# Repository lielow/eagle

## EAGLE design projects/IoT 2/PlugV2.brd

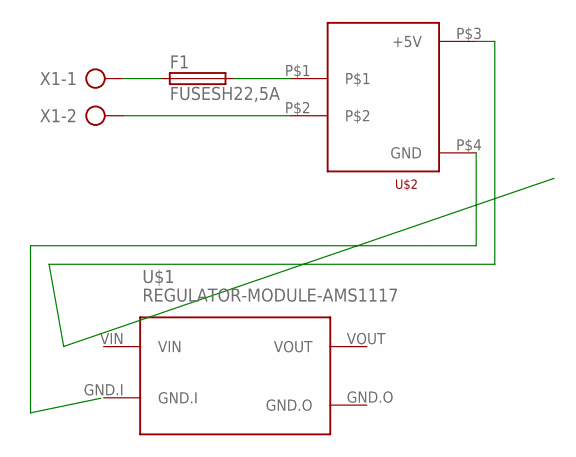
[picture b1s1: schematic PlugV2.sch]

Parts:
F1: FUSESH22,5A; SH22,5A
U$1: REGULATOR-MODULE-AMS1117
U$2: HLK-PM01
X1: AK300/2

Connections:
unnamed: F1.1, X1.1
unnamed: U$2.P$2, X1.2
unnamed: F1.2, U$2.P$1

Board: 2 copper layers, 4 parts (0 on the bottom side), 3 nets, no tracks yet.

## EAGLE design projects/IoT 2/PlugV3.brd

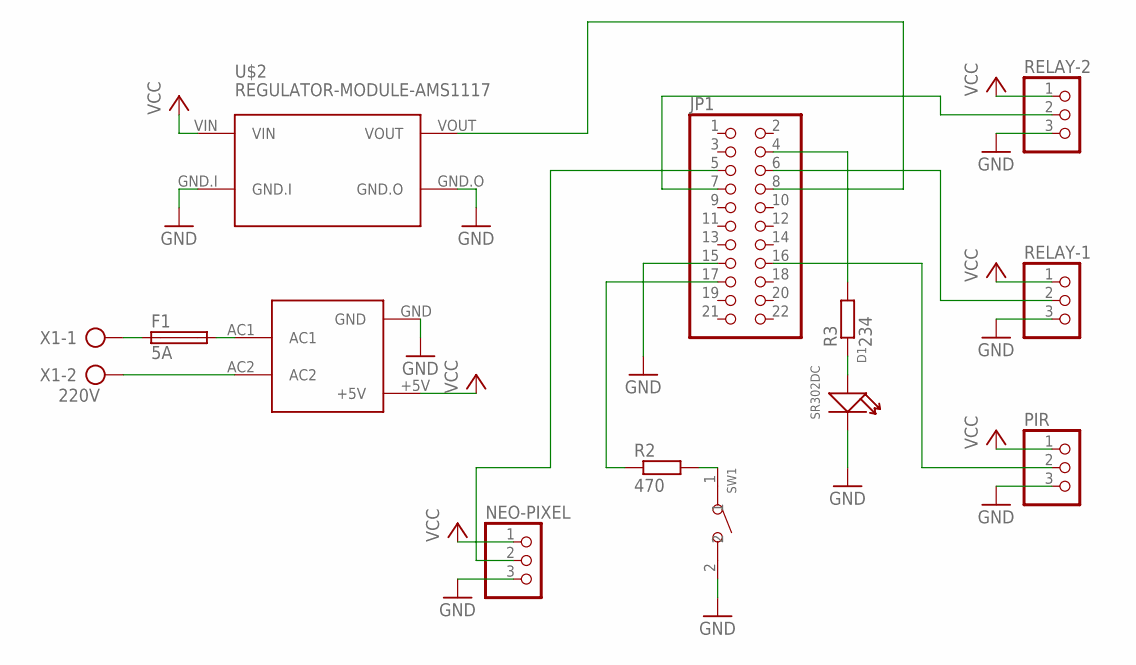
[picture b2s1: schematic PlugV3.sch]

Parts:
D1: SR302DC; LED2-2.54-D3.0MM
F1: 5A; SH22,5A
JP1: PINHD-2X11; 2X11
NEO-PIXEL: PINHD-1X3; 1X03
PIR: PINHD-1X3; 1X03
R2: 470; 0207/7
R3: 234; 0207/7
RELAY-1, RELAY-2: PINHD-1X3; 1X03
SW1: DIP-BUTTON(2P-6.0X3.0X4.3MM)-TS-1101F; SW2-5.0-6.0X3.0X4.3MM
U$1: HLK-PM01
U$2: REGULATOR-MODULE-AMS1117
X1: 220V; AK300/2

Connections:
GND: D1.K (-), JP1.15, NEO-PIXEL.3, PIR.3, RELAY-1.3, RELAY-2.3, SW1.2, U$1.GND, U$2.GND.I, U$2.GND.O
unnamed: F1.1, X1.1
unnamed: F1.2, U$1.AC1
unnamed: U$1.AC2, X1.2
unnamed: JP1.8, U$2.VOUT
unnamed: JP1.16, PIR.2
unnamed: JP1.6, RELAY-1.2
unnamed: JP1.7, RELAY-2.2
unnamed: JP1.5, NEO-PIXEL.2
unnamed: JP1.17, R2.1
unnamed: R2.2, SW1.1
unnamed: JP1.4, R3.2
unnamed: D1.A (+), R3.1
VCC: NEO-PIXEL.1, PIR.1, RELAY-1.1, RELAY-2.1, U$1.+5V, U$2.VIN

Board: 2 copper layers, 13 parts (0 on the bottom side), 14 nets, no tracks yet.

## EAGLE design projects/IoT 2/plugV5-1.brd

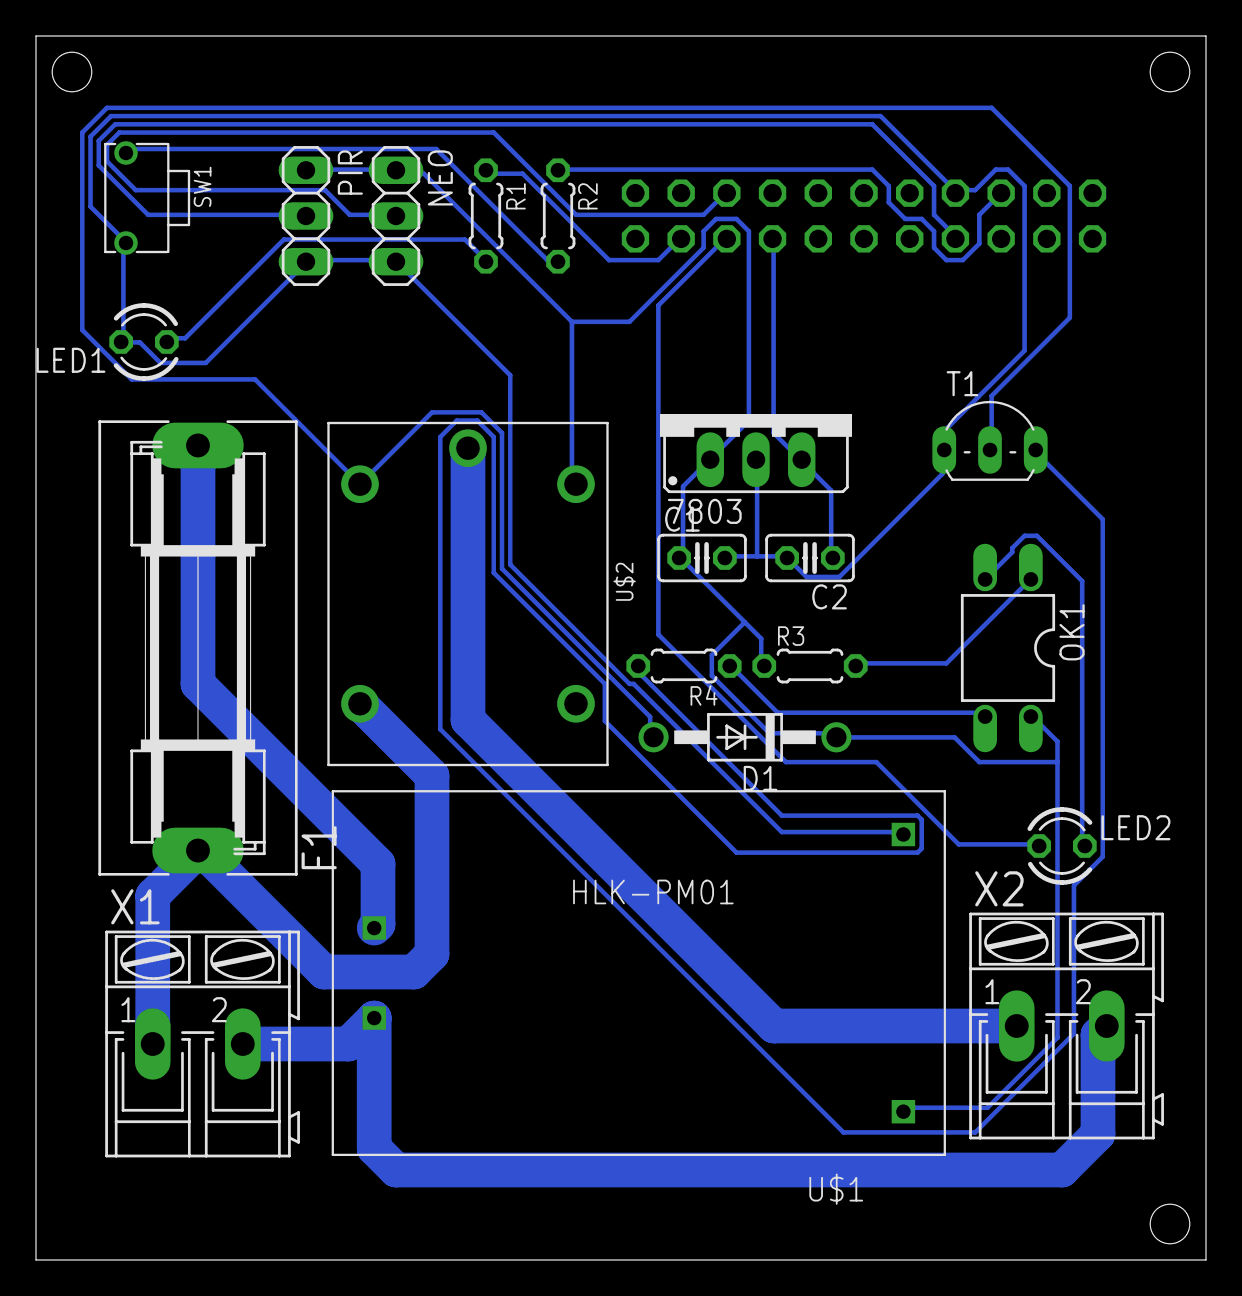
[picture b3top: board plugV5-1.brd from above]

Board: 2 copper layers, 65.0 x 68.0 mm, 21 parts (1 on the bottom side), 19 nets.

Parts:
7803: 5to3.3V; 78XXS
C1: 0.33uF; C025-025X050
C2: 0.1uF; C025-025X050
D1: 1N4004; DO41-10
F1: 5A; SH22,5A
LED1: RED; LED3MM
LED2: LED3MM
NEO: 1X03
OK1: PC817; DIL04
PIR: 1X03
R1: 230; 0204/5
R2: 470; 0204/5
R3: 1k; 0204/5
R4: 510; 0204/5
SOCKET: esp8266; 2X11
SW1: SW2-5.0-6.0X3.0X4.3MM
T1: 2SC458; TO92-ECB
U$1: HLK-PM01
U$2: RELAY-SONGLE
X1: 220V; AK300/2
X2: Plug; AK300/2

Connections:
+3V3: 7803.OUT, C2.1, SOCKET.8
+5V: 7803.IN, C1.1, D1.C, NEO.1, OK1.4, PIR.1, R3.1, U$1.+5V, U$2.V+
GND: 7803.GND, C1.2, C2.2, LED1.K, NEO.3, PIR.3, SOCKET.15, SW1.2, T1.E, U$1.GND
unnamed: F1.1, U$2.NO, X1.1
unnamed: F1.2, U$1.AC1
unnamed: U$1.AC2, X1.2, X2.2
unnamed: U$2.COM, X2.1
unnamed: LED1.A, R1.2
unnamed: R1.1, SOCKET.4
unnamed: PIR.2, SOCKET.16
unnamed: NEO.2, SOCKET.5
unnamed: R2.2, SW1.1
unnamed: R2.1, SOCKET.17
unnamed: OK1.1, R3.2
unnamed: LED2.A, SOCKET.6
unnamed: LED2.K, OK1.2
unnamed: OK1.3, R4.1
unnamed: R4.2, T1.B
unnamed: D1.A, T1.C, U$2.V-

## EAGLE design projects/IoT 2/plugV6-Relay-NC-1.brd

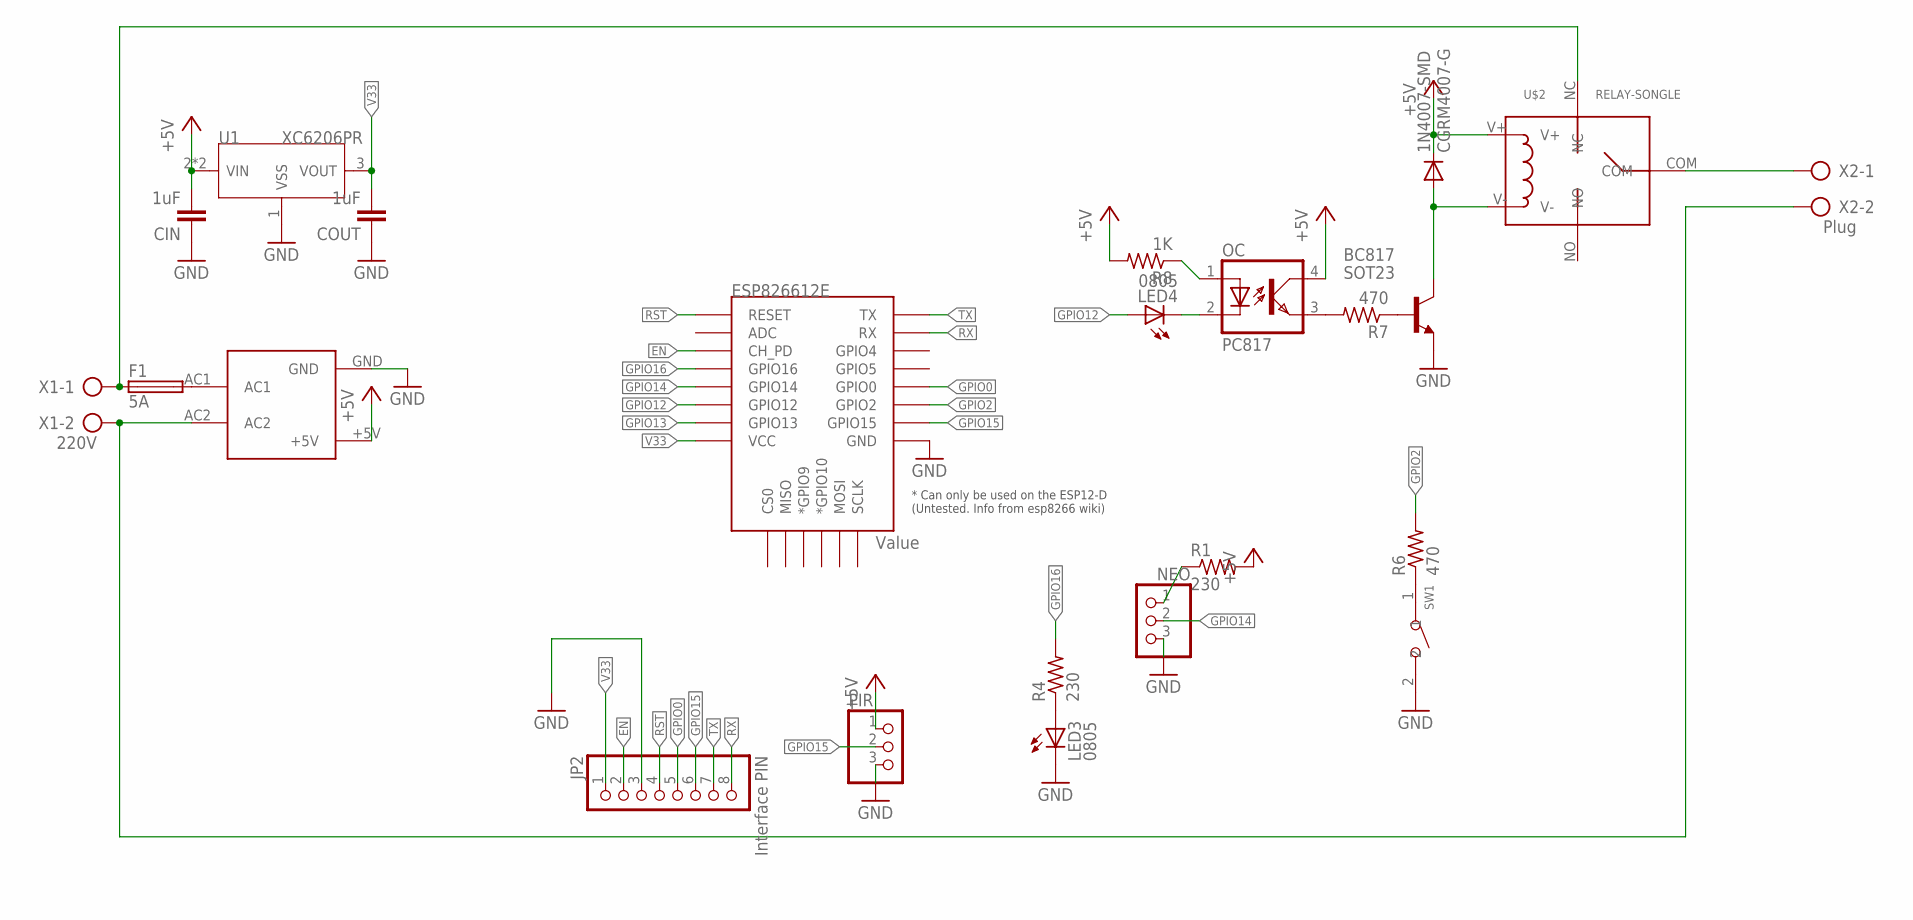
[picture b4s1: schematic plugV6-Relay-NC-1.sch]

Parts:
1N4007-SMD: CGRM4007-G; SOD-123_MINI-SMA
BC817: SOT23; SOT23-BEC
CIN: 1uF; C0805
COUT: 1uF; C0805
ESP826612E: Value; ESP12E-SMD
F1: 5A; SH22,5A
JP2: Interface PIN; 1X08
LED3, LED4: 0805; CHIP-LED0603
NEO: PINHD-1X3; 1X03
OC: PC817; DIL04
PIR: PINHD-1X3; 1X03
R1, R4: 230; R1206
R6, R7: 470; R1206
R8: 1K; R1206
SW1: DIP-BUTTON(2P-6.0X3.0X4.3MM)-TS-1101F; SW2-5.0-6.0X3.0X4.3MM
U1: XC6206PR; SOT89
U$1: HLK-PM01
U$2: RELAY-SONGLE
X1: 220V; AK300/2
X2: Plug; AK300/2

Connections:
+5V: 1N4007-SMD.C, CIN.2, OC.4 (COL), PIR.1, R1.2, R8.2, U1.2 (VIN), U1.4 (VIN), U$1.+5V, U$2.V+
EN: ESP826612E.CH_PD, JP2.2
GND: BC817.E, CIN.1, COUT.1, ESP826612E.GND, JP2.3, LED3.C, NEO.3, PIR.3, SW1.2, U1.1 (VSS), U$1.GND
GPIO0: ESP826612E.GPIO0, JP2.5
GPIO2: ESP826612E.GPIO2, R6.2
GPIO12: ESP826612E.GPIO12, LED4.A
GPIO13: ESP826612E.GPIO13
GPIO14: ESP826612E.GPIO14, NEO.2
GPIO15: ESP826612E.GPIO15, JP2.6, PIR.2
GPIO16: ESP826612E.GPIO16, R4.2
unnamed: F1.1, U$2.NC, X1.1
unnamed: F1.2, U$1.AC1
unnamed: U$1.AC2, X1.2, X2.2
unnamed: U$2.COM, X2.1
unnamed: OC.3 (EMIT), R7.2
unnamed: BC817.B, R7.1
unnamed: R6.1, SW1.1
unnamed: LED3.A, R4.1
unnamed: NEO.1, R1.1
unnamed: OC.1 (A), R8.1
unnamed: LED4.C, OC.2 (C)
unnamed: 1N4007-SMD.A, BC817.C, U$2.V-
RST: ESP826612E.RESET, JP2.4
RX: ESP826612E.RXD0 (RX), JP2.8
TX: ESP826612E.TXD0 (TX), JP2.7
V33: COUT.2, ESP826612E.VCC, JP2.1, U1.3 (VOUT)

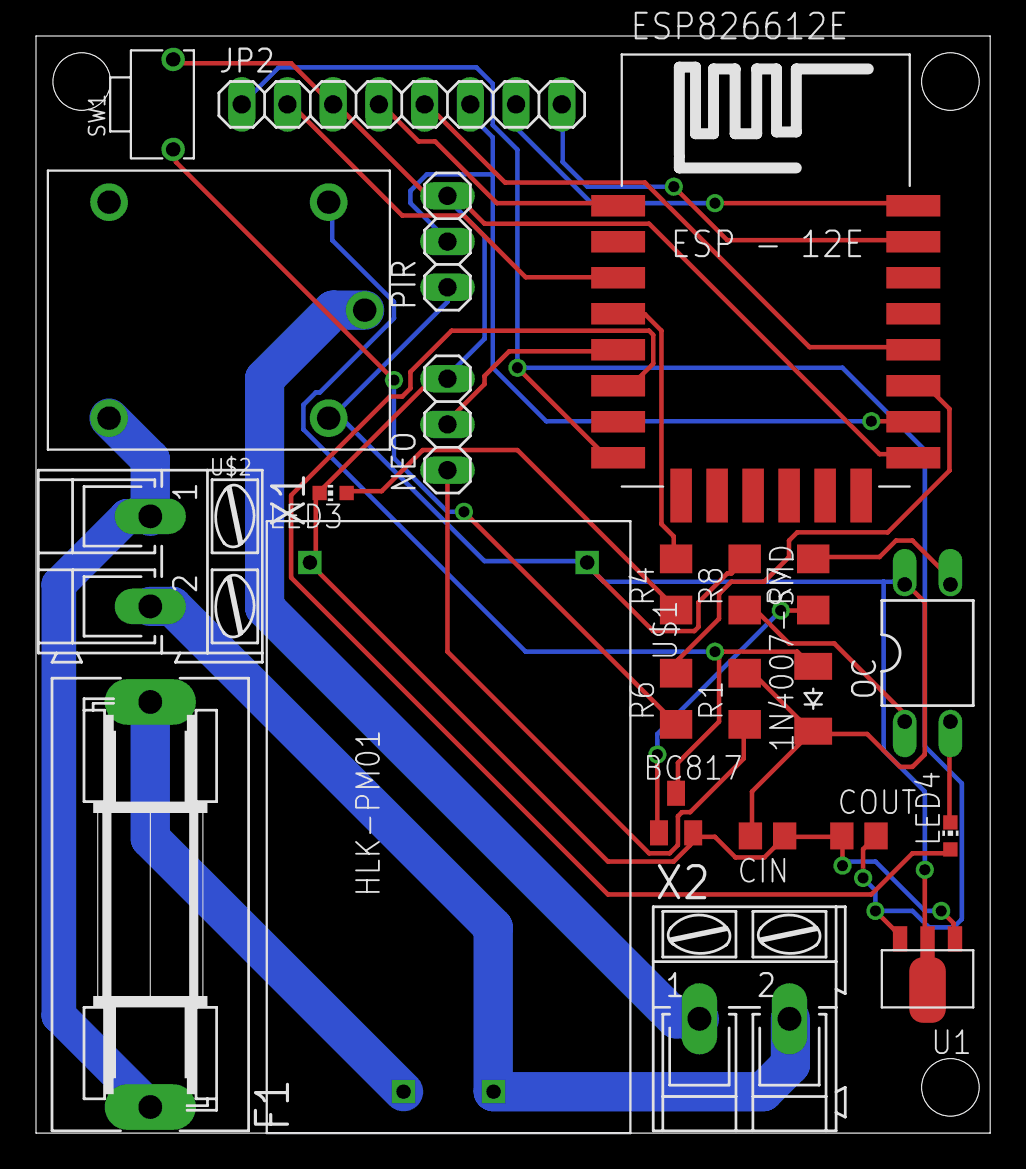
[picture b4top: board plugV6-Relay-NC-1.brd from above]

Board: 2 copper layers, 53.0 x 61.0 mm, 23 parts (0 on the bottom side), 25 nets.
